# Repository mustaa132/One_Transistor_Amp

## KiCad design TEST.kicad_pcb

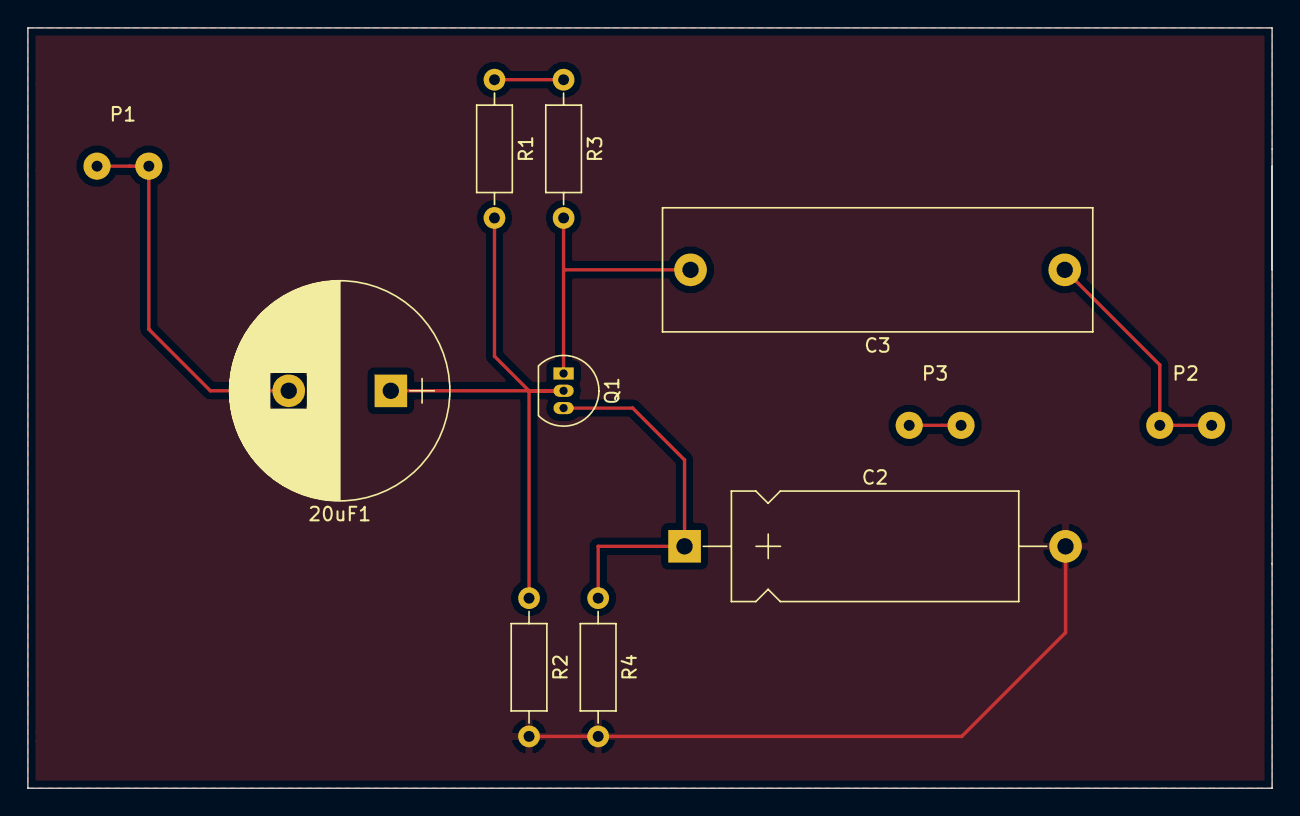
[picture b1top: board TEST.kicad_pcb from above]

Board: 2 copper layers, 91.4 x 55.9 mm, 11 parts (0 on the bottom side), 7 nets.

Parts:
20uF1: C; CP_Radial_D16.0mm_P7.50mm
C2: 50uF; CP_Axial_L21.0mm_D8.0mm_P28.00mm_Horizontal
C3: 20uF; C_Rect_L31.5mm_W9.0mm_P27.50mm_MKS4
P1: Signal_İn; SolderWirePad_2x_0-8mmDrill
P2, P3: Sıgnal_Out; SolderWirePad_2x_0-8mmDrill
Q1: BC548; TO-92_Inline_Narrow_Oval
R1: 22k; R_Axial_DIN0207_L6.3mm_D2.5mm_P10.16mm_Horizontal
R2: 6,8k; R_Axial_DIN0207_L6.3mm_D2.5mm_P10.16mm_Horizontal
R3: 4,7k; R_Axial_DIN0207_L6.3mm_D2.5mm_P10.16mm_Horizontal
R4: 1,8k; R_Axial_DIN0207_L6.3mm_D2.5mm_P10.16mm_Horizontal

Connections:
+12C: R1.1, R3.1
GND: C2.2, R2.2, R4.2
unnamed: 20uF1.1, Q1.2, R1.2, R2.1
unnamed: 20uF1.2, P1.1
unnamed: C2.1, Q1.3, R4.1
unnamed: C3.1, P2.1
unnamed: C3.2, Q1.1, R3.2

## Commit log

2017-03-25 one transistor circuit homework
2017-05-11 added folders
2017-05-24 mustafa_yıldız_one_transıstor_amp_all
